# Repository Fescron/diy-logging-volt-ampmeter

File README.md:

# DIY Logging Volt/Ampmeter

<br/>

<br/>

| Quick access links | |
|------|-----|
| [Carrier board v1.0 schematic (PDF)](hardware/high-accuracy-logging-volt-ampmeter/high-accuracy-logging-volt-ampmeter.pdf) | [Doxygen code documentation of individual files and methods](https://fescron.github.io/diy-logging-volt-ampmeter/files.html) |
| [Wiring diagram v1.0 (PDF)](hardware/wiring-diagram_diy-logging-volt-ampmeter/wiring-diagram_diy-logging-volt-ampmeter.pdf) | [Doxygen TODO's](https://fescron.github.io/diy-logging-volt-ampmeter/todo.html) |

<br/>

This battery-powered logging volt/ampmeter was made with the intention to easily get `.CSV` files filled with voltage/current/power measurements on a SD-card to plot and use this data further. It is supposed to have the same functionality as much more expensive dataloggers, with the added benefit of the ability to change the firmware to add more functions.

<br/>

## 0 - Table of Contents

- [DIY Logging Volt/Ampmeter](#diy-logging-voltampmeter)
  - [0 - Table of Contents](#0---table-of-contents)
  - [1 - Construction](#1---construction)
  - [2 - Usage](#2---usage)
  - [3 - Bash script to generate plots (logplot)](#3---bash-script-to-generate-plots-logplot)
  - [4 - Additional hardware changes (carrier board v1.0)](#4---additional-hardware-changes-carrier-board-v10)
  - [5 - Future code-additions](#5---future-code-additions)

<br/>

## 1 - Construction

<br/>

The device consists of **two Chinese** (but very accurate and highly functional) **meters** ([BY56W 50V](https://aliexpress.com/item/32840631947.html) and [BY56W 5A](https://aliexpress.com/item/32839044728.html)) with independent power-supplies so no *common-mode* errors can occur. They can be individually powered on or off with **toggle switches** left of these meters. On the right of them are **combination banana- and screw-terminals** to easily connect measurement cables. The black and red one are the negative and positive terminal of the voltmeter, the blue and yellow one are the negative and positive terminal of the current meter. In series with the latter plugs and the current meter are a **5A 5x10mm fuse** (fitted in a holder on right right side of the logger), along with an **5V internal NC-relay** (with a [5V boostconverter](https://aliexpress.com/item/32891706812.html) and protection-diode) to open the current connection in certain scenarios (over-voltage, over-current, under-voltage, ...). Currently no code is written to use this relay functionality.

On the bottom a **third module** with the same shell as the voltage and current meters (I asked the Chinese store if they could sell me some) is situated with **two [1.3" 128x64 I2C OLED-displays](https://aliexpress.com/item/32830144222.html)** and a **STM32 Blue-Pill board** (with a genuine (!) ST `STM32F103C8T6` microcontroller). This functions as the brains of the whole unit. This bottom module can also be switched on or off with the **toggle switch** to the left. The display-module *asks* the two meters for measurement values and does additional conversions and calculations with them, drives the displays, keeps the time with its **internal RTC and 3V coincell backup-battery**, reads the battery voltage, outputs the measurements to the UART port on top, ... Next to the bottom module an **up/down monostable toggle switch** and **[pressable rotary encoder](https://aliexpress.com/item/32915420023.html)** can be used to start or stop logging, view measurements, change settings, ...

This module however **does not write the data to a SD-card directly**. For this a **[Sparkfun OpenLog](https://www.sparkfun.com/products/13712) module** has to be plugged in to the **external UART port on top**. Because of the way the firmware is developed, a new `.TXT` file is created each time a new measurement-session is started. The resulting file can be easily renamed to a `.CSV` file to facilitate importing in *Excel* or *OpenOffice Calc*. The first line of the file contains a header which explains what data goes where in the following measurement-lines. The last two lines of the file contain another header with corresponding data like date, total runtime, capacity and maximum/minimum values.

The whole thing is powered by **two (parallel) 18650 batteries** in a [battery holder](https://aliexpress.com/item/32832636191.html). A [charge and battery-protection PCB](https://aliexpress.com/item/32666559864.html) facilitates charging at 1A using **USB Type-C** on the left side of the meter. I used a [breakout-board](https://aliexpress.com/item/4001299632280.html) with two 5.1k resistors on the `CC1` and `CC2` pins to activate the 5V output on USB-PD compliant chargers. Above this Type-C port ***charging* and *done* LED's** are also fitted. Right of this the **programming-port** and two **external GPIO-pins** with a 3.3V and GND terminal on *Dupont*-connectors are situated. These two external GPIO-pins however currently have no function. Internally there also is a **buzzer** which can be used to signal various states, but no code is written to use this functionality as well. Some buck-boost converters (after the toggle switches) are also placed on a prototype-PCB to convert the battery voltage to 5V (with [these boostconverters](https://aliexpress.com/item/32891706812.html)) for the meters and 3.3V (with [this buck/boostconverter](https://aliexpress.com/item/32822323191.html)) for the bottom STM32-display-module.

The picture below depicts the internal wiring-diagram, standalone modules/boards are surrounded in blue frames.

<br/>

<br/>

## 2 - Usage

The **up/down monostable toggle-switch** and **pressable rotary encoder** on the right of the bottom display-module are used to switch between display-pages and to set various settings.

The **left display** always indicates the power on the top. If the display is selected (*selection-line* drawn on the bottom of the display) the rotary encoder can be used to switch between the different pages to display additional information: max/min voltage, max/min current and calculated capacity in Ah and Wh. Upon an encoder-press the displayed information can be reset (if the logger is not saving data to a SD-card). Below these three available pages on the left display are depicted.

<br/>

A down-press on the monostable toggle-switch changes the selected display. The *selection-line* on the bottom of the display will be moved to the newly selected display.

The **right display** always indicates the internal battery voltage and state of the logger (`STOP/START/RUN/SAVE`) on the top. If this display is selected (*selection-line* drawn on the bottom of the display) the rotary encoder can again be used to switch between the different pages to display additional information. The first page displays the current date and time, and pressing the encoder enables the user to change this information. Values are changed by rotating the encoder, the value (for example the day) is saved on an encoder-press, and the next item (for example the month) can now be edited. The second page displays the period between measurements saved to the logfile with the external logger. Pressing the encoder activates the ability to change the period by rotating the encoder, pressing it again saves the value. The third page displays the runtime if the logger is saving data to the external logger. Below these three available pages on the right display are depicted.

<br/>

An up-press on the monostable toggle switch (if the logger is in `STOP`-mode) powers-up the external logger (`START`) and writes the *header*, along with a first measurement-line to the `.TXT` file (`SAVE`). Then the logger waits (`RUN`) until the measurement-period runs out and writes another measurement to the file (`SAVE`). Another up-press on the monostable toggle switch stops the logging and writes two more lines to the end of the file including data as the date, total runtime, capacity, max/min values, ... An example of the resulting data in such a `.TXT` file is depicted below.

```
Time [hour:min:sec],Runtime [hour:min:sec],Voltage [V],Current [A],Power [W]
17:46:21,00:00:01,1.291,0.0000,0.000
17:46:23,00:00:03,1.291,0.0000,0.000
17:46:25,00:00:05,1.291,0.0000,0.000
17:46:27,00:00:07,1.291,0.0000,0.000
17:46:29,00:00:09,0.875,0.0000,0.000
17:46:31,00:00:11,1.092,0.0000,0.000
17:46:33,00:00:13,1.290,0.0000,0.000
Date [day/month/year],Runtime [hour:min:sec],Capacity [Ah],Capacity [Wh],Max Volt [V],Min Volt [V],Max Curr [A],Min Curr [A]
17/08/2021,00:00:13,00.000,00.000,01.291,00.000,0.0000,0.0000
```

<br/>

## 3 - Bash script to generate plots (logplot)

To easily convert the `.txt`/`.csv` files from this meter and get **plots in PDF-form**, a bash-script using `gnuplot` and `ps2pdf`/`imagemagick` was created. To create a PDF-plot of a file (`LOG00110.TXT`) with the title "Title" and subtitle "Subtitle", and to make sure the capacity and max/min voltage and current values are displayed above the graph, one can use the following command:

```bash
logplot -f "LOG00110.TXT" -t "Title" -st "Subtitle" -av
```

<br/>

Below is a list of all of the possible commands, which can also be shown with the command `logplot -h`. The bash-script itself can be found [here](software/logplot)

<br/>

## 4 - Additional hardware changes (carrier board v1.0)

To simplify the firmware for the rotary encoder logic some pins were swapped around on header `J9` and `J11`. This is highlighted by bold text on the wiring-diagram on the **STM32F103C8T6 board**.

Unfortunately a wrong MOSFET was used for the function to power the external Openlog UART datalogger on or off. This means that MCU pin `UART1-ENout/PB8` is unused and a **PMOS bodge PCB** was constructed. This can be seen on the wiring-diagram. MCU pin `PB14` is used instead to power the logger.

<br/>

## 5 - Future code-additions

The firmware is constructed with a lot of extra variables to facilitate the functionality to only update changed values on the displays. This speeds up the code but does however create a lot of *overhead*. In the future this can certainly be optimized.

As of yet not all of the hardware is used, like for example the relay and buzzer. All TODO's can be found in the [Doxygen TODO's](https://fescron.github.io/diy-logging-volt-ampmeter/todo.html).

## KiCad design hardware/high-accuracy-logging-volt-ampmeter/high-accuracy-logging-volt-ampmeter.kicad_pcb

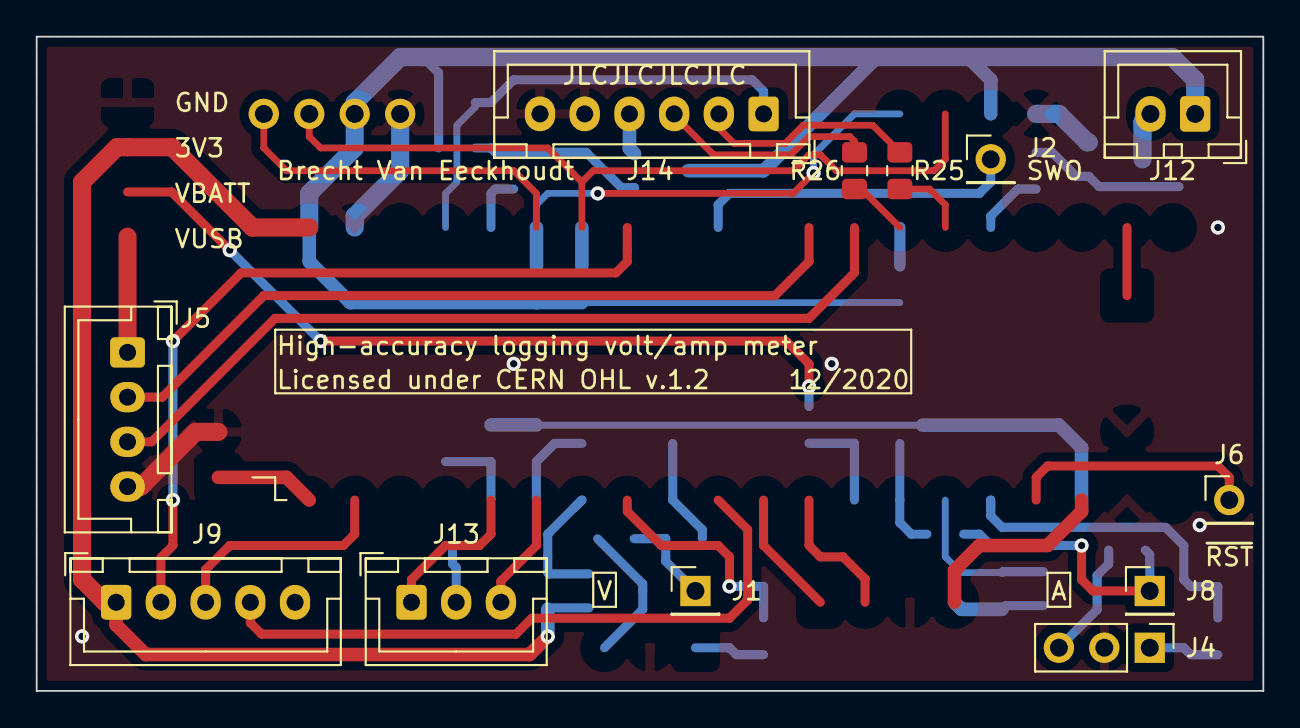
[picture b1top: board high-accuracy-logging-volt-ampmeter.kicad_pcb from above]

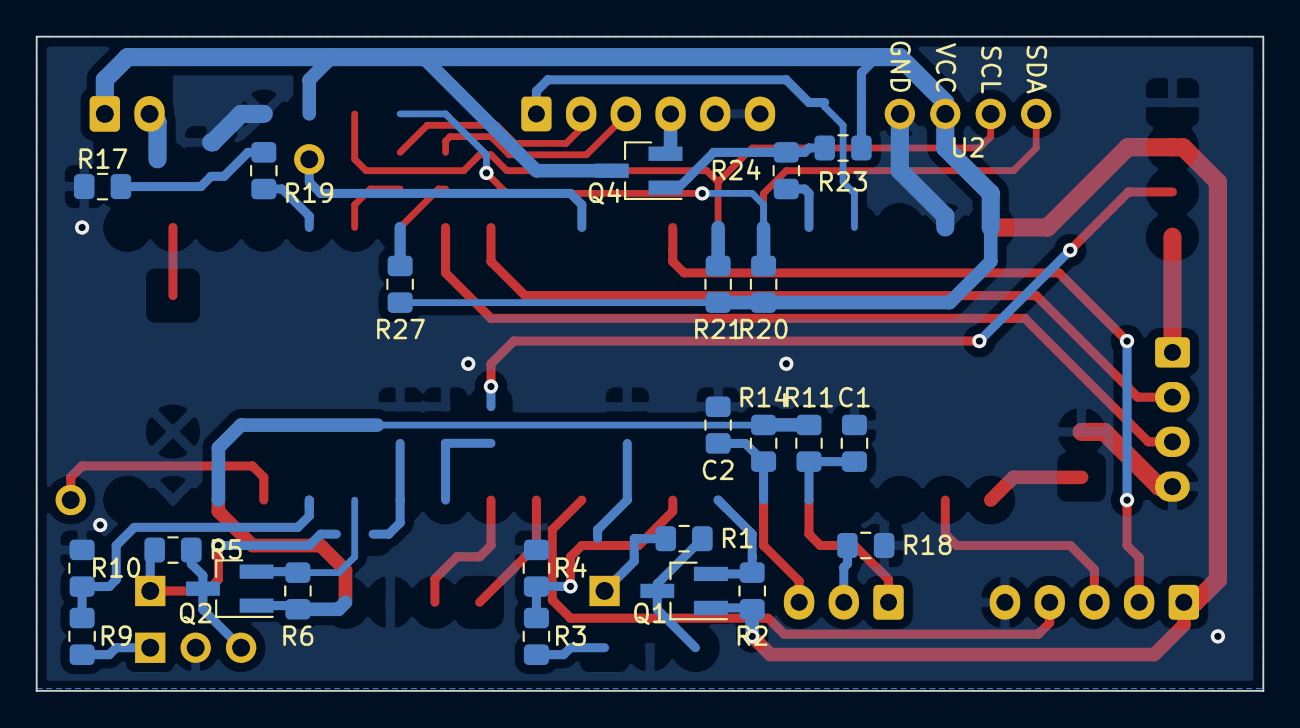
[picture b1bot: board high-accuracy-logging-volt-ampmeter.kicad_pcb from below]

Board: 2 copper layers, 68.6 x 36.6 mm, 37 parts (24 on the bottom side), 22 nets.

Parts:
C1, C2: 100 nF; C_0805_2012Metric_Pad1.15x1.40mm_HandSolder
G1: Symbol_OSHW-Logo_11.4x12mm; OSHW-Logo_5.7x6mm_SolderMask
J1: 5Vin-Voltage; PinHeader_1x01_P2.54mm_Vertical
J2: SWO; PinHeader_1x01_P2.54mm_Vertical
J4: BY56W Voltage; PinHeader_1x03_P2.54mm_Vertical
J5: USB; JST_XH_B4B-XH-A_1x04_P2.50mm_Vertical
J6: ~RESET; PinHeader_1x01_P2.54mm_Vertical
J8: 5Vin-Current; PinHeader_1x01_P2.54mm_Vertical
J9: Encoder; JST_XH_B5B-XH-A_1x05_P2.50mm_Vertical
J12: Relay; JST_XH_B2B-XH-A_1x02_P2.50mm_Vertical
J13: Switch; JST_XH_B3B-XH-A_1x03_P2.50mm_Vertical
J14: UART Out; JST_XH_B6B-XH-A_1x06_P2.50mm_Vertical
Q1, Q2, Q4: 2N7002-7-F; SOT-23_Handsoldering
R1, R2, R5, R6, R11, R14, R17, R20, R21, R23, R27: 10 kΩ; R_0805_2012Metric_Pad1.15x1.40mm_HandSolder
R3, R9, R18: 1 kΩ; R_0805_2012Metric_Pad1.15x1.40mm_HandSolder
R4, R10: 2 kΩ; R_0805_2012Metric_Pad1.15x1.40mm_HandSolder
R19, R24, R25, R26: 100 Ω; R_0805_2012Metric_Pad1.15x1.40mm_HandSolder
U2: 1.3; 1.3INCH-128x64-I2C-OLED-NoHoles

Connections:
/3V3: J9.1, J12.1, Q1.1, Q2.1, Q4.3, R2.1, R6.2, R11.1, R14.2, R20.1, R21.1, R23.1, R27.1, U2.2
/A-5Vin: J8.1, R5.1
/GND: C1.1, C2.2, J4.2, J5.4, J9.5, J14.5, J14.6, R4.2, R10.2, R17.2, R18.2, U2.1
/RXD1_3V3: R26.2, R27.2
/RXD2_3V3: R3.2, R4.1
/RXD3_3V3: R9.2, R10.1
/RXD3_5V: J4.1, R9.1
/SCL1_3V3: R21.2, U2.3
/SDA1_3V3: R20.2, U2.4
/SW0: C1.2, J13.1, R11.2
/SW1: C2.1, J13.3, R14.1
/TXD2_3V3: Q1.2, R2.2
/TXD2_5V: Q1.3, R1.1
/TXD3_3V3: Q2.2, R6.1
/TXD3_5V: J4.3, Q2.3, R5.2
/UART1-3V3: J14.4, Q4.2
/V-5Vin: J1.1, R1.2
unnamed: J13.2, R18.1
unnamed: J14.2, R25.2
unnamed: J14.3, R26.1
unnamed: R17.1, R19.2
unnamed: Q4.1, R23.2, R24.2

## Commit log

2021-09-01 Added hardware v1.0 files
2021-09-01 Added pictures
2021-09-01 Added gitignore
2021-09-01 Added, doxyfile
2021-09-02 Added firmware v1.0 files
2021-09-02 Added Doxygen documentation
2021-09-03 Added wiring diagram
2021-09-03 Added display-pictures
2021-09-03 Added README
2021-09-03 Moved Doxygen files
2021-12-08 Added logplot bash-script
2021-12-08 Updated logplot-script code (added more functionality)
2021-12-08 Updated readme to reflect changes in script
2021-12-09 Updated logplot script
2021-12-09 Updated logplot help-picture
2021-12-10 Started printing date before time and removed day-printing on last line
2021-12-10 Updated Doxygen documentation
2021-12-10 Updated script to reflect new logfile format
2021-12-12 Changed default measurement period to 10s
2021-12-12 Updated TODO's
2021-12-12 Updated wiring diagram with new power-conversion board with power path
2021-12-12 Updated wiring-diagram png
2021-12-13 Compared floats more reliably and implemented data-check
2022-04-03 Added option to handle files with no footer

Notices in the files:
hardware/high-accuracy-logging-volt-ampmeter/high-accuracy-logging-volt-ampmeter.kicad_pcb:
Licensed under CERN OHL v.1.2
